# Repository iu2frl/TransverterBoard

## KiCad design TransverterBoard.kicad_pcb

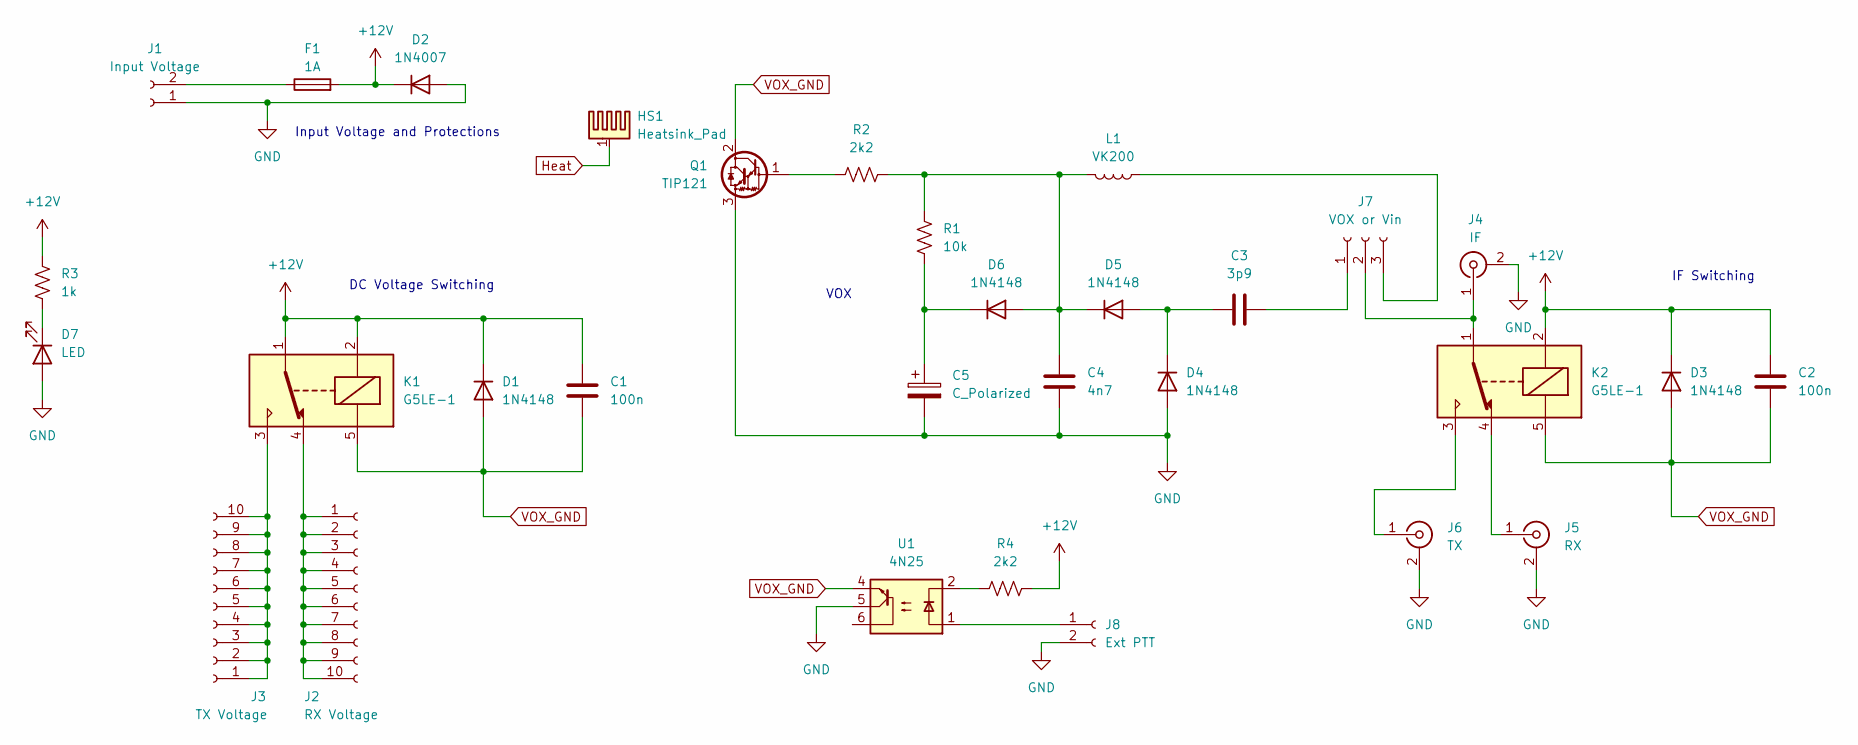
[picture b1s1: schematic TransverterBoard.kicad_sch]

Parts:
C1, C2: 100n; C_Disc_D7.5mm_W2.5mm_P5.00mm
C3: 3p9; C_Disc_D7.5mm_W2.5mm_P5.00mm
C4: 4n7; C_Disc_D7.5mm_W2.5mm_P5.00mm
C5: C_Polarized; CP_Radial_D6.3mm_P2.50mm
D1, D3, D4, D5, D6: 1N4148; D_DO-35_SOD27_P7.62mm_Horizontal
D2: 1N4007; D_DO-41_SOD81_P10.16mm_Horizontal
D7: LED; LED_D3.0mm_Clear
F1: 1A; Fuseholder_Littelfuse_100_series_5x20mm
HS1: Heatsink_Pad; Heatsink_35x26mm_1xFixation3mm_Fischer-SK486-35
J1: Input Voltage; PinHeader_1x02_P2.54mm_Vertical
J2: RX Voltage; PinHeader_1x10_P2.54mm_Vertical
J3: TX Voltage; PinHeader_1x10_P2.54mm_Vertical
J4: IF; SMA_Amphenol_132289_EdgeMount
J5: RX; SMA_Amphenol_132289_EdgeMount
J6: TX; SMA_Amphenol_132289_EdgeMount
J7: VOX or Vin; PinHeader_1x03_P2.54mm_Vertical
J8: Ext PTT; PinHeader_1x02_P2.54mm_Vertical
K1, K2: G5LE-1; Relay_SPDT_Omron-G5LE-1
L1: VK200; L_Axial_L20.0mm_D8.0mm_P5.08mm_Vertical
Q1: TIP121; TO-220-3_Horizontal_TabDown
R1: 10k; R_Axial_DIN0207_L6.3mm_D2.5mm_P10.16mm_Horizontal
R2, R4: 2k2; R_Axial_DIN0207_L6.3mm_D2.5mm_P10.16mm_Horizontal
R3: 1k; R_Axial_DIN0207_L6.3mm_D2.5mm_P10.16mm_Horizontal
U1: 4N25; DIP-6_W7.62mm

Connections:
+12V: C1.1, C2.1, D1.1 (K), D2.1 (K), D3.1 (K), F1.2, K1.1, K1.2, K2.2, R3.1, R4.2
GND: C4.1, C5.2, D2.2 (A), D4.2 (A), D7.2 (A), J1.1, J4.2 (Ext), J5.2 (Ext), J6.2 (Ext), J8.2, Q1.3 (E), U1.5
unnamed: C3.1, D4.1 (K), D5.2 (A)
unnamed: C4.2, D5.1 (K), D6.2 (A), L1.2, R1.1, R2.2
unnamed: C5.1, D6.1 (K), R1.2
unnamed: D7.1 (K), R3.2
unnamed: F1.1, J1.2
unnamed: J2.1, J2.2, J2.3, J2.4, J2.5, J2.6, J2.7, J2.8, J2.9, J2.10, K1.4
unnamed: J3.1, J3.2, J3.3, J3.4, J3.5, J3.6, J3.7, J3.8, J3.9, J3.10, K1.3
unnamed: J4.1 (In), J7.2, K2.1
unnamed: J5.1 (In), K2.4
unnamed: J6.1 (In), K2.3
unnamed: C3.2, J7.1
unnamed: J7.3, L1.1
unnamed: J8.1, U1.1
unnamed: Q1.1 (B), R2.1
unnamed: R4.1, U1.2
VOX_GND: C1.2, C2.2, D1.2 (A), D3.2 (A), K1.5, K2.5, Q1.2 (C), U1.4

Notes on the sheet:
VOX
Input Voltage and Protections
DC Voltage Switching
IF Switching

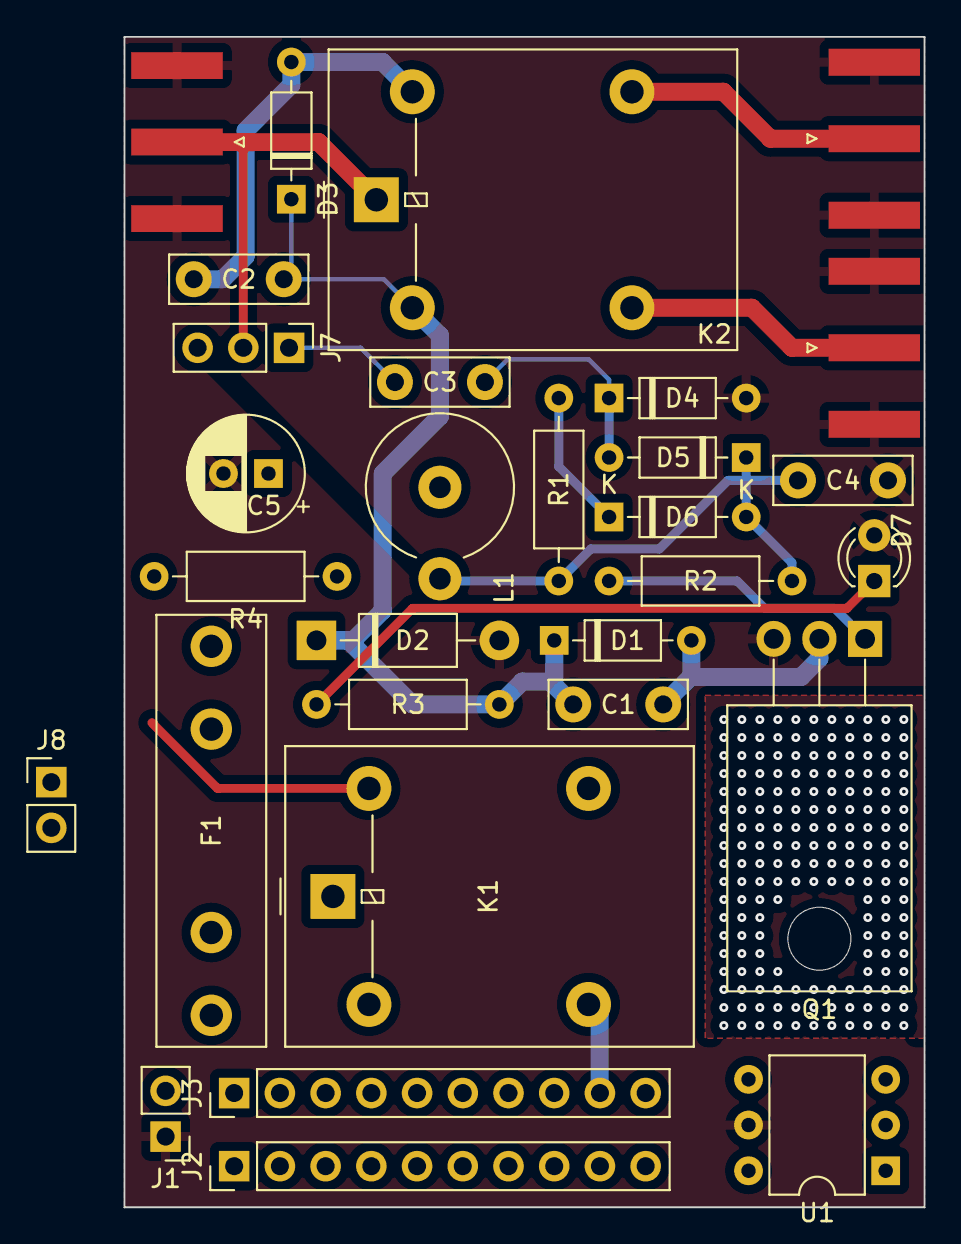
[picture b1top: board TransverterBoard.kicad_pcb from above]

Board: 2 copper layers, 44.4 x 65.0 mm, 30 parts (0 on the bottom side), 18 nets.

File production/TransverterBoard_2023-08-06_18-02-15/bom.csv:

Designator,Footprint,Quantity,Value,LCSC Part #
"C1, C2",C_Disc_D7.5mm_W2.5mm_P5.00mm,2,100n,
C3,C_Disc_D7.5mm_W2.5mm_P5.00mm,1,3p9,
C4,C_Disc_D7.5mm_W2.5mm_P5.00mm,1,4n7,
C5,CP_Radial_D6.3mm_P2.50mm,1,C_Polarized,
"D1, D3, D4, D5, D6",D_DO-35_SOD27_P7.62mm_Horizontal,5,1N4148,
D2,D_DO-41_SOD81_P10.16mm_Horizontal,1,1N4007,
D7,LED_D3.0mm_Clear,1,LED,
F1,Fuseholder_Littelfuse_100_series_5x20mm,1,1A,
J1,PinHeader_1x02_P2.54mm_Vertical,1,Input Voltage,
J2,PinHeader_1x10_P2.54mm_Vertical,1,RX Voltage,
J3,PinHeader_1x10_P2.54mm_Vertical,1,TX Voltage,
J4,SMA_Amphenol_132289_EdgeMount,1,IF,
J5,SMA_Amphenol_132289_EdgeMount,1,RX,
J6,SMA_Amphenol_132289_EdgeMount,1,TX,
J7,PinHeader_1x03_P2.54mm_Vertical,1,VOX or Vin,
"K1, K2",Relay_SPDT_Omron-G5LE-1,2,G5LE-1,
L1,L_Axial_L20.0mm_D8.0mm_P5.08mm_Vertical,1,VK200,
Q1,TO-220-3_Horizontal_TabDown,1,TIP121,
R1,R_Axial_DIN0207_L6.3mm_D2.5mm_P10.16mm_Horizontal,1,10k,
R2,R_Axial_DIN0207_L6.3mm_D2.5mm_P10.16mm_Horizontal,1,2k2,
R3,R_Axial_DIN0207_L6.3mm_D2.5mm_P10.16mm_Horizontal,1,1k,

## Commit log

2023-08-06 First draft
2023-08-08 working
